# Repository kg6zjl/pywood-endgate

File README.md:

Our scouting troop in TrailLifeUSA needs a way to identify which Pinewood Derby cars place first and second. We run two brackets, one for first place and one for second. Our current track is a 4 lane with manually operated lever gate for release.

I decided that from a K.I.S.S. standpoint, I don't care about timing the cars. Could be a future state, but for this iteration it doesn't matter. We really only care about the order that the cars reach the end gate.

This is my first time ever working at a PIO/hardware level, so feedback is appreciated. I'm learning along the way!

# Initial Design
- Micropython as the language
- Waveshare RP2040 Plus as the MCU
- 4 Row LCD for results
- A momentary reset button to trigger a display reset
- Light Dependent Resistors (Digital Module LM393) under the track, existing light source in endgate as primary light source

# Future State/Improvements/Ideas
- Add duplicate display at start gate so that bracket manager can see results on stage
- Add a microswitch at the start gate and add timing functionality
- Print race slips for winners with times? could be fun
- A camera/photo of the winner would be fun, especially if we setup a projector
- Automated bracket tracking?
- IR Break Beam sensors for end gate (introduces slightly more wiring, but same amount of programatic complexity I think)

# Notes
- When loading up RP2040, you have to load MicroPython first (see firmware)
- Then you have to copy all the project files over to RP2040
- Click "Run" in VSCode

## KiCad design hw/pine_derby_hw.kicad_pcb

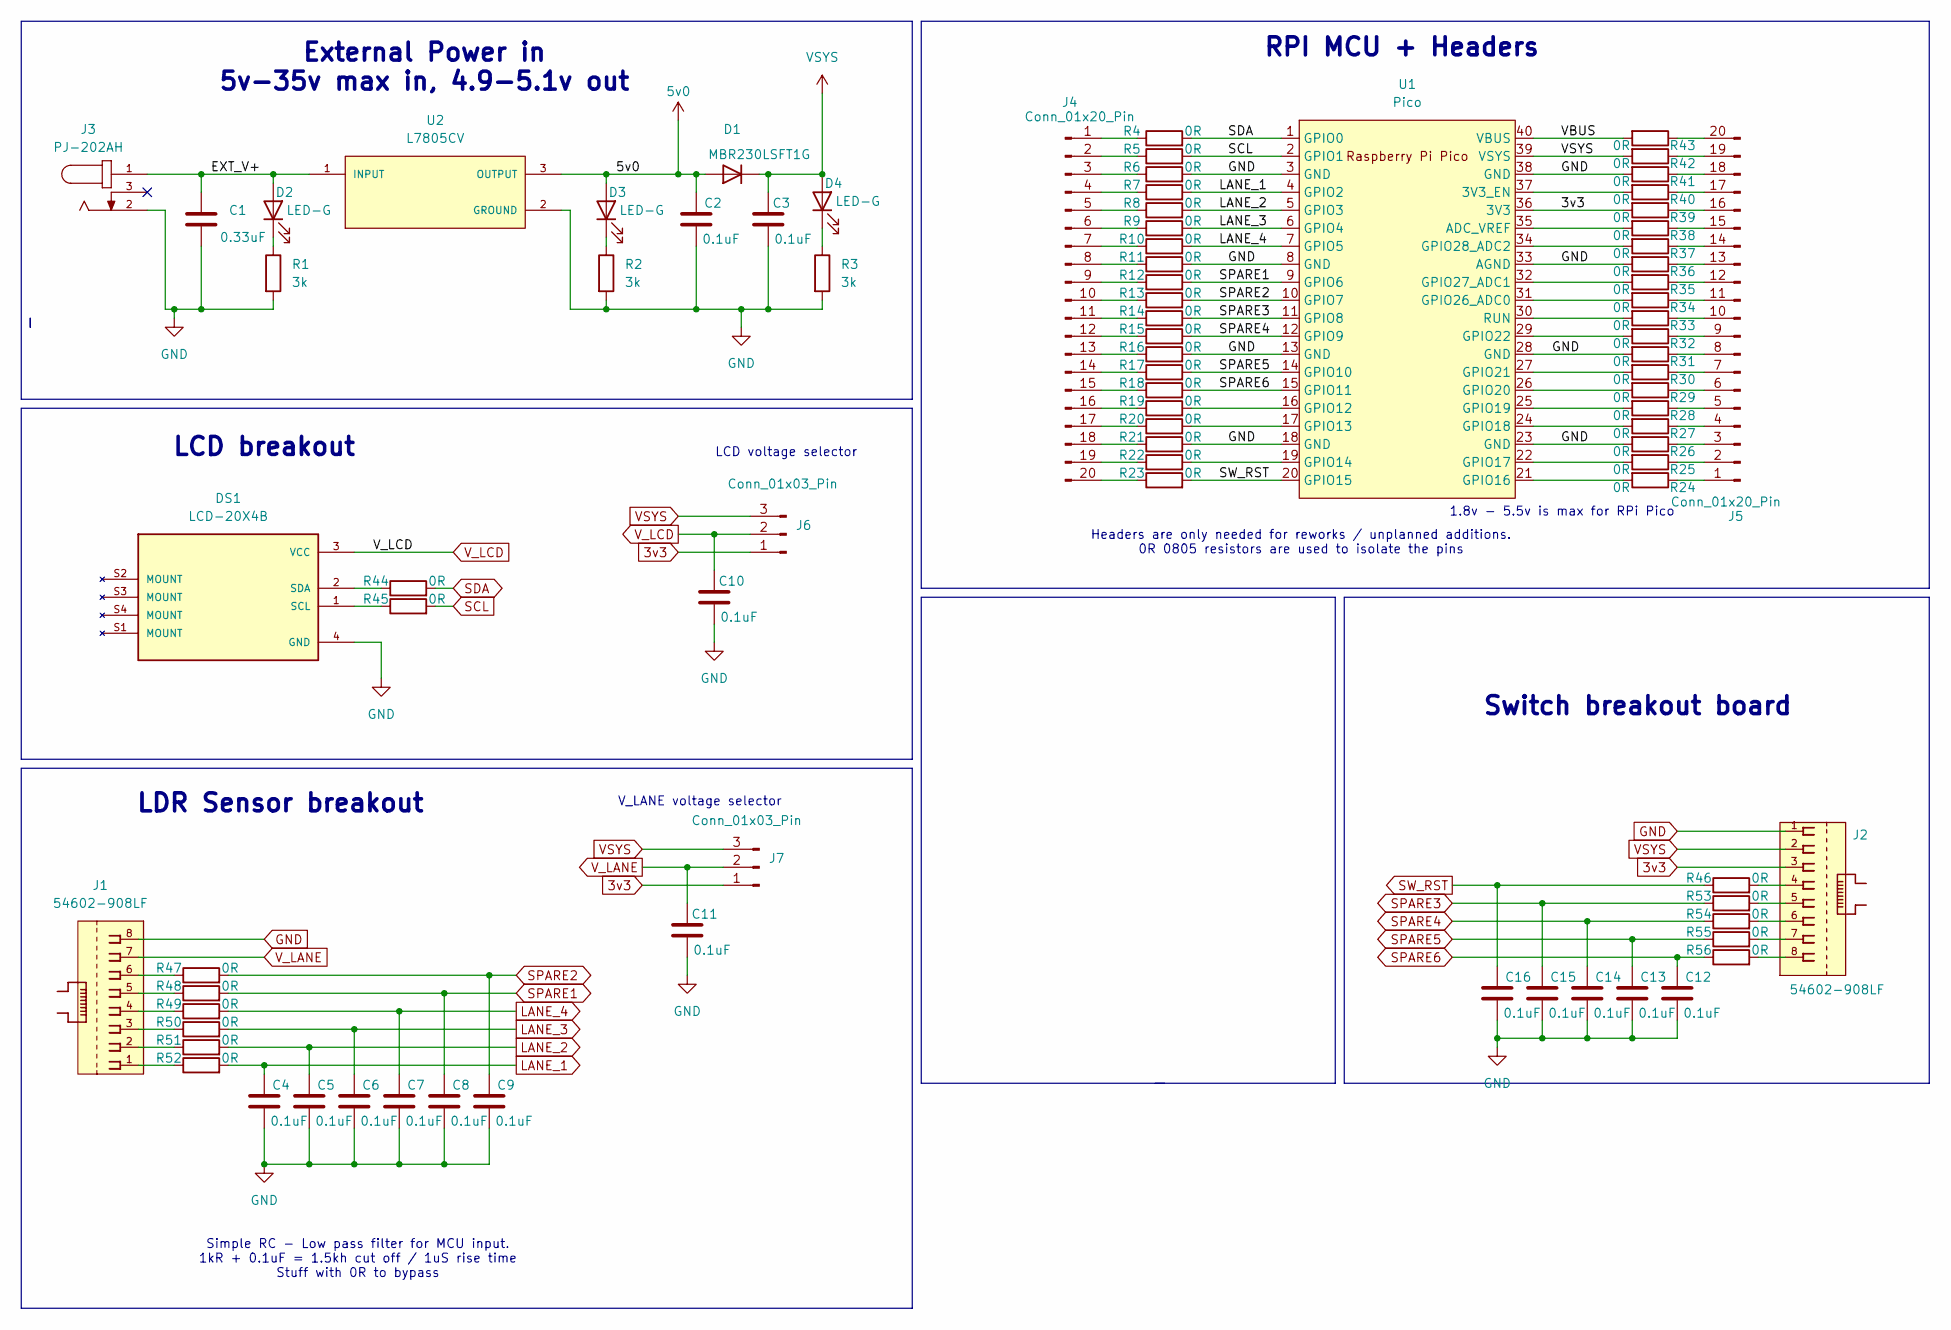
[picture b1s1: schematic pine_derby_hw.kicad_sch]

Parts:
C1: 0.33uF; C_1206_3216Metric_Pad1.33x1.80mm_HandSolder; MPN CL31B334KBFNNNE
C2, C3, C4, C5, C6, C7, C8, C9, C10, C11, C12, C13, C14, C15, C16: 0.1uF; C_1206_3216Metric_Pad1.33x1.80mm_HandSolder; MPN 1206B104K500CT
D1: D; Nexperia_CFP3_SOD-123W; MPN MBR230LSFT1G
D2, D3, D4: LED-G; LED_1206_3216Metric_Pad1.42x1.75mm_HandSolder; forward voltage 2.1v; MPN LTST-C150GKT
DS1: LCD-20X4B; LCD_LCD-20X4B
J1, J2: 54602-908LF; AMPHENOL_54602-908LF; PARTREV J
J3: PJ-202AH; CUI_PJ-202AH; PART_REV 1.02
J4, J5: Conn_01x20_Pin; PinHeader_1x20_P2.54mm_Vertical; MPN PH1-20-UA
J6, J7: Conn_01x03_Pin; PinHeader_1x03_P2.54mm_Vertical; MPN 61300311121
R1, R2, R3: 3k; R_1206_3216Metric_Pad1.30x1.75mm_HandSolder; MPN RC1206JR-073KL
R4, R5, R6, R7, R8, R9, R10, R11, R12, R13, R14, R15, R16, R17, R18, R19, R20, R21, R22, R23, R24, R25, R26, R27, R28, R29, R30, R31, R32, R33, R34, R35, R36, R37, R38, R39, R40, R41, R42, R43, R44, R45, R46, R47, R48, R49, R50, R51, R52, R53, R54, R55, R56: 0R; R_0805_2012Metric_Pad1.20x1.40mm_HandSolder; MPN RC0805JR-070RL
U1: Pico; RPi_Pico_SMD_TH
U2: L7805CV; TO255P1040X460X1968-3; PARTREV 36

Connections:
3v3: J2.3, J6.1, J7.1, R39.2, U1.36 (3V3)
5v0: C2.1, D1.2 (A), D3.2 (A), U2.3 (OUTPUT)
/EXT_V+: C1.1, D2.2 (A), J3.1, U2.1 (INPUT)
/VBUS: R43.2, U1.40 (VBUS)
GND: C1.2, C2.2, C3.2, C4.2, C5.2, C6.2, C7.2, C8.2, C9.2, C10.2, C11.2, C12.2, C13.2, C14.2, C15.2, C16.2, DS1.4 (GND), J1.8, J2.1, J3.2, R1.2, R2.2, R3.2, R6.2, R11.2, R16.2, R21.2, R26.2, R31.2, R36.2, R41.2, U1.3 (GND), U1.8 (GND), U1.13 (GND), U1.18 (GND), U1.23 (GND), U1.28 (GND), U1.33 (AGND), U1.38 (GND), U2.2 (GROUND)
LANE_1: C4.1, R7.2, R52.2, U1.4 (GPIO2)
LANE_2: C5.1, R8.2, R51.2, U1.5 (GPIO3)
LANE_3: C6.1, R9.2, R50.2, U1.6 (GPIO4)
LANE_4: C7.1, R10.2, R49.2, U1.7 (GPIO5)
unnamed: D2.1 (K), R1.1
unnamed: D3.1 (K), R2.1
unnamed: D4.1 (K), R3.1
unnamed: DS1.1 (SCL), R45.1
unnamed: DS1.2 (SDA), R44.1
unnamed: J1.1, R52.1
unnamed: J1.2, R51.1
unnamed: J1.3, R50.1
unnamed: J1.4, R49.1
unnamed: J1.5, R48.1
unnamed: J1.6, R47.1
unnamed: J2.4, R46.2
unnamed: J2.5, R53.2
unnamed: J2.6, R54.2
unnamed: J2.7, R55.2
unnamed: J2.8, R56.2
unnamed: J4.1, R4.1
unnamed: J4.2, R5.1
unnamed: J4.3, R6.1
unnamed: J4.4, R7.1
unnamed: J4.5, R8.1
unnamed: J4.6, R9.1
unnamed: J4.7, R10.1
unnamed: J4.8, R11.1
unnamed: J4.9, R12.1
unnamed: J4.10, R13.1
unnamed: J4.11, R14.1
unnamed: J4.12, R15.1
unnamed: J4.13, R16.1
unnamed: J4.14, R17.1
unnamed: J4.15, R18.1
unnamed: J4.16, R19.1
unnamed: J4.17, R20.1
unnamed: J4.18, R21.1
unnamed: J4.19, R22.1
unnamed: J4.20, R23.1
unnamed: J5.1, R24.1
unnamed: J5.2, R25.1
unnamed: J5.3, R26.1
unnamed: J5.4, R27.1
unnamed: J5.5, R28.1
unnamed: J5.6, R29.1
unnamed: J5.7, R30.1
unnamed: J5.8, R31.1
unnamed: J5.9, R32.1
unnamed: J5.10, R33.1
unnamed: J5.11, R34.1
unnamed: J5.12, R35.1
unnamed: J5.13, R36.1
unnamed: J5.14, R37.1
unnamed: J5.15, R38.1
unnamed: J5.16, R39.1
unnamed: J5.17, R40.1
unnamed: J5.18, R41.1
unnamed: J5.19, R42.1
unnamed: J5.20, R43.1
unnamed: R40.2, U1.37 (3V3_EN)
unnamed: R38.2, U1.35 (ADC_VREF)
unnamed: R19.2, U1.16 (GPIO12)
unnamed: R20.2, U1.17 (GPIO13)
unnamed: R22.2, U1.19 (GPIO14)
unnamed: R24.2, U1.21 (GPIO16)
unnamed: R25.2, U1.22 (GPIO17)
unnamed: R27.2, U1.24 (GPIO18)
unnamed: R28.2, U1.25 (GPIO19)
unnamed: R29.2, U1.26 (GPIO20)
unnamed: R30.2, U1.27 (GPIO21)
unnamed: R32.2, U1.29 (GPIO22)
unnamed: R34.2, U1.31 (GPIO26_ADC0)
unnamed: R35.2, U1.32 (GPIO27_ADC1)
unnamed: R37.2, U1.34 (GPIO28_ADC2)
unnamed: R33.2, U1.30 (RUN)
SCL: R5.2, R45.2, U1.2 (GPIO1)
SDA: R4.2, R44.2, U1.1 (GPIO0)
SPARE1: C8.1, R12.2, R48.2, U1.9 (GPIO6)
SPARE2: C9.1, R13.2, R47.2, U1.10 (GPIO7)
SPARE3: C15.1, R14.2, R53.1, U1.11 (GPIO8)
SPARE4: C14.1, R15.2, R54.1, U1.12 (GPIO9)
SPARE5: C13.1, R17.2, R55.1, U1.14 (GPIO10)
SPARE6: C12.1, R18.2, R56.1, U1.15 (GPIO11)
SW_RST: C16.1, R23.2, R46.1, U1.20 (GPIO15)
VSYS: C3.1, D1.1 (K), D4.2 (A), J2.2, J6.3, J7.3, R42.2, U1.39 (VSYS)
V_LANE: C11.1, J1.7, J7.2
V_LCD: C10.1, DS1.3 (VCC), J6.2

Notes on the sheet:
LCD breakout
Simple RC - Low pass filter for MCU input. 1kR + 0.1uF = 1.5kh cut off / 1uS rise time Stuff with 0R to bypass
1.8v - 5.5v is max for RPi Pico
Headers are only needed for reworks / unplanned additions. 0R 0805 resistors are used to isolate the pins
Switch breakout board
LDR Sensor breakout
External Power in 5v-35v max in, 4.9-5.1v out
LCD voltage selector
V_LANE voltage selector
RPI MCU + Headers

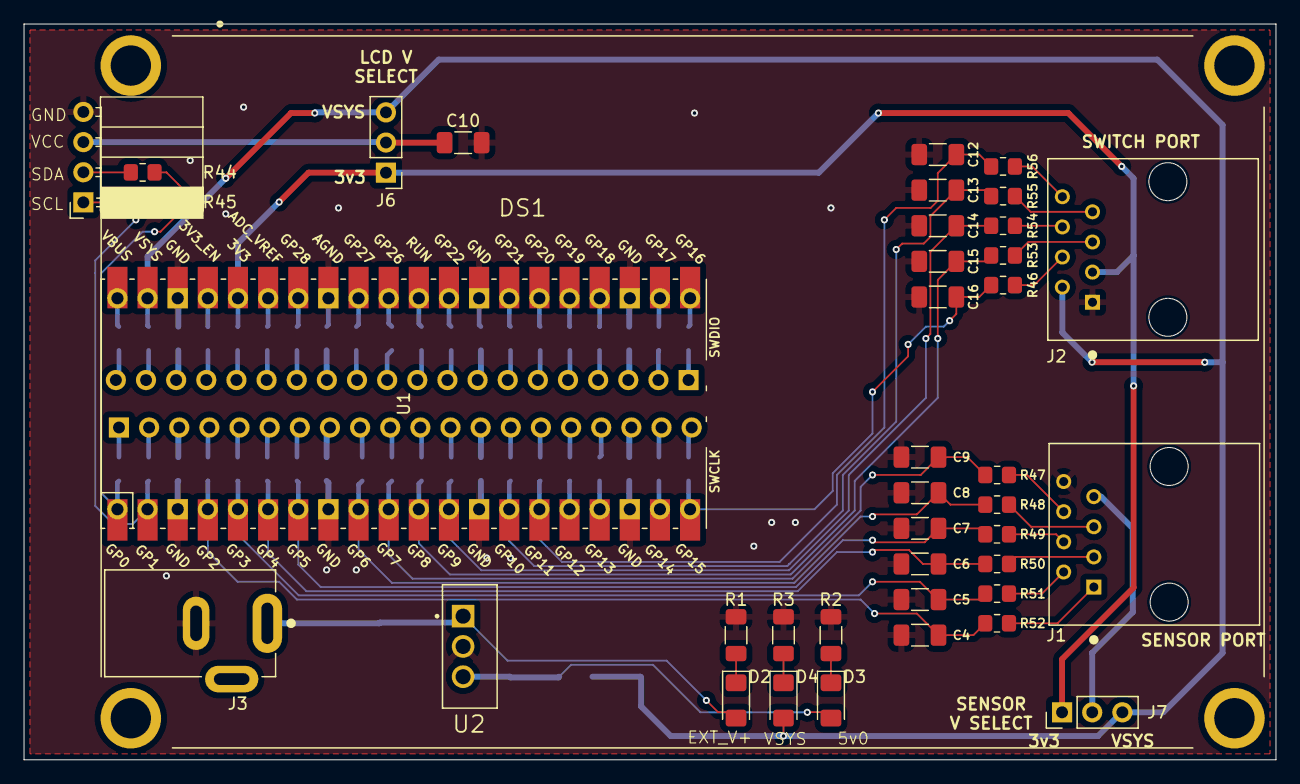
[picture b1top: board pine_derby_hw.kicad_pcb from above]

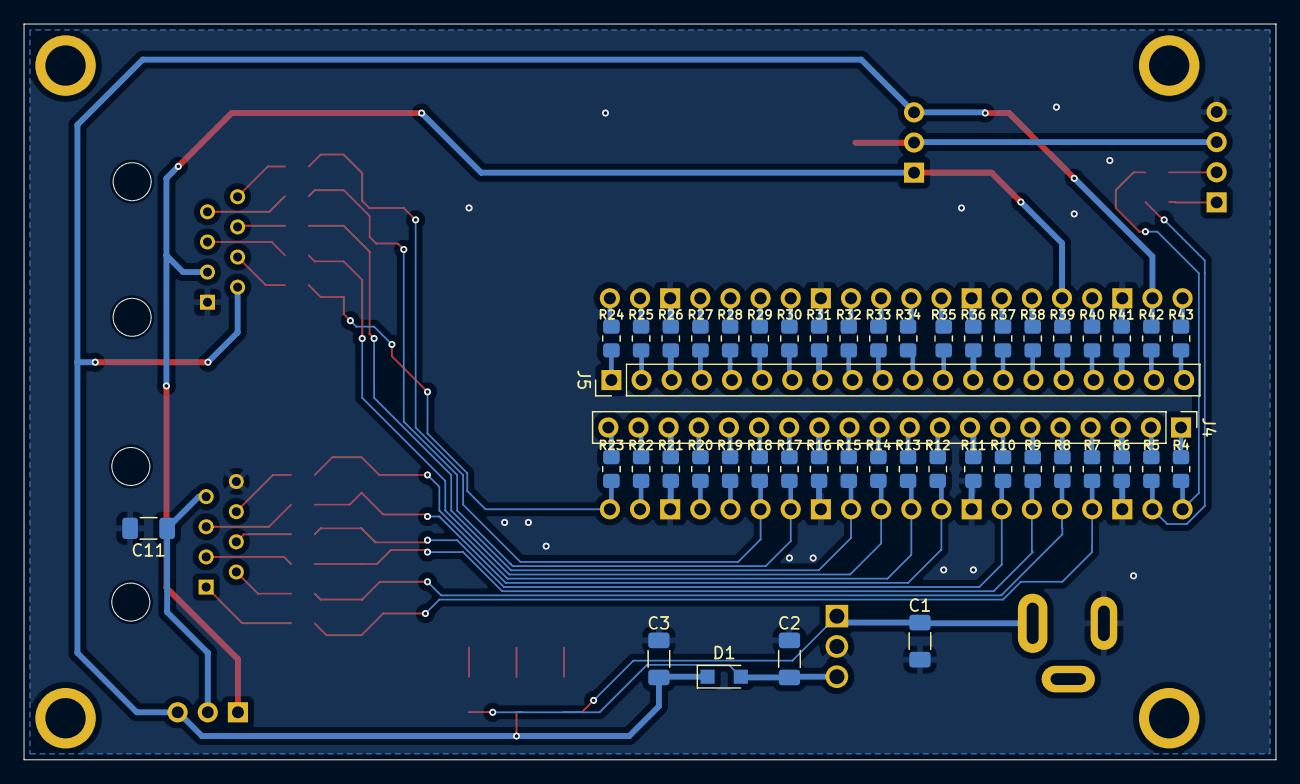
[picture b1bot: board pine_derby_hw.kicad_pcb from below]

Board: 2 copper layers, 105.5 x 62.0 mm, 86 parts (47 on the bottom side), 93 nets.

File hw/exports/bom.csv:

"Reference","Value","Datasheet","Footprint","Qty","DNP","MPN"
"J3","PJ-202AH","~","PJ-202AH:CUI_PJ-202AH","1","","PJ-202AH"
"U2","L7805CV","","L7805CV:TO255P1040X460X1968-3","1","","L7805C-V"
"J1,J2","54602-908LF","","54602-908LF:AMPHENOL_54602-908LF","2","","54602-908LF"
"U1","Pico","","MCU_RaspberryPi_and_Boards:RPi_Pico_SMD_TH","1","",""
"R4,R5,R6,R7,R8,R9,R10,R11,R12,R13,R14,R15,R16,R17,R18,R19,R20,R21,R22,R23,R24,R25,R26,R27,R28,R29,R30,R31,R32,R33,R34,R35,R36,R37,R38,R39,R40,R41,R42,R43,R44,R45,R46,R47,R48,R49,R50,R51,R52,R53,R54,R55,R56","0R","~","Resistor_SMD:R_0805_2012Metric_Pad1.20x1.40mm_HandSolder","53","","RC0805JR-070RL"
"R1,R2,R3","3k","~","Resistor_SMD:R_1206_3216Metric_Pad1.30x1.75mm_HandSolder","3","","RC1206JR-073KL"
"J6,J7","Conn_01x03_Pin","~","Connector_PinHeader_2.54mm:PinHeader_1x03_P2.54mm_Vertical","2","","61300311121"
"J4,J5","Conn_01x20_Pin","~","Connector_PinHeader_2.54mm:PinHeader_1x20_P2.54mm_Vertical","2","","PH1-20-UA"
"DS1","LCD-20X4B","","LCD-20X48:LCD_LCD-20X4B","1","",""
"D2,D3,D4","LED-G","~","LED_SMD:LED_1206_3216Metric_Pad1.42x1.75mm_HandSolder","3","","LTST-C150GKT"
"D1","D","~","Diode_SMD:Nexperia_CFP3_SOD-123W","1","","MBR230LSFT1G"
"C2,C3,C4,C5,C6,C7,C8,C9,C10,C11,C12,C13,C14,C15,C16","0.1uF","~","Capacitor_SMD:C_1206_3216Metric_Pad1.33x1.80mm_HandSolder","15","","1206B104K500CT"
"C1","0.33uF","~","Capacitor_SMD:C_1206_3216Metric_Pad1.33x1.80mm_HandSolder","1","","CL31B334KBFNNNE"

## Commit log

2024-08-27 Init commit for micropython based endgate to track how each lane places
2024-08-27 Add renovate.json
2024-08-27 use ldr pin map to write lane number to RANK
2024-08-27 Update main.py
    define clock output pin
2024-08-28 adding LCD and basic networking config
2024-09-12 functioning copy with 4 LDRs and LCD, without any networking
2025-01-21 updating ignores
2025-01-23 adding networking features and hardware spec
2025-01-26 sensors on interrupts and networking
